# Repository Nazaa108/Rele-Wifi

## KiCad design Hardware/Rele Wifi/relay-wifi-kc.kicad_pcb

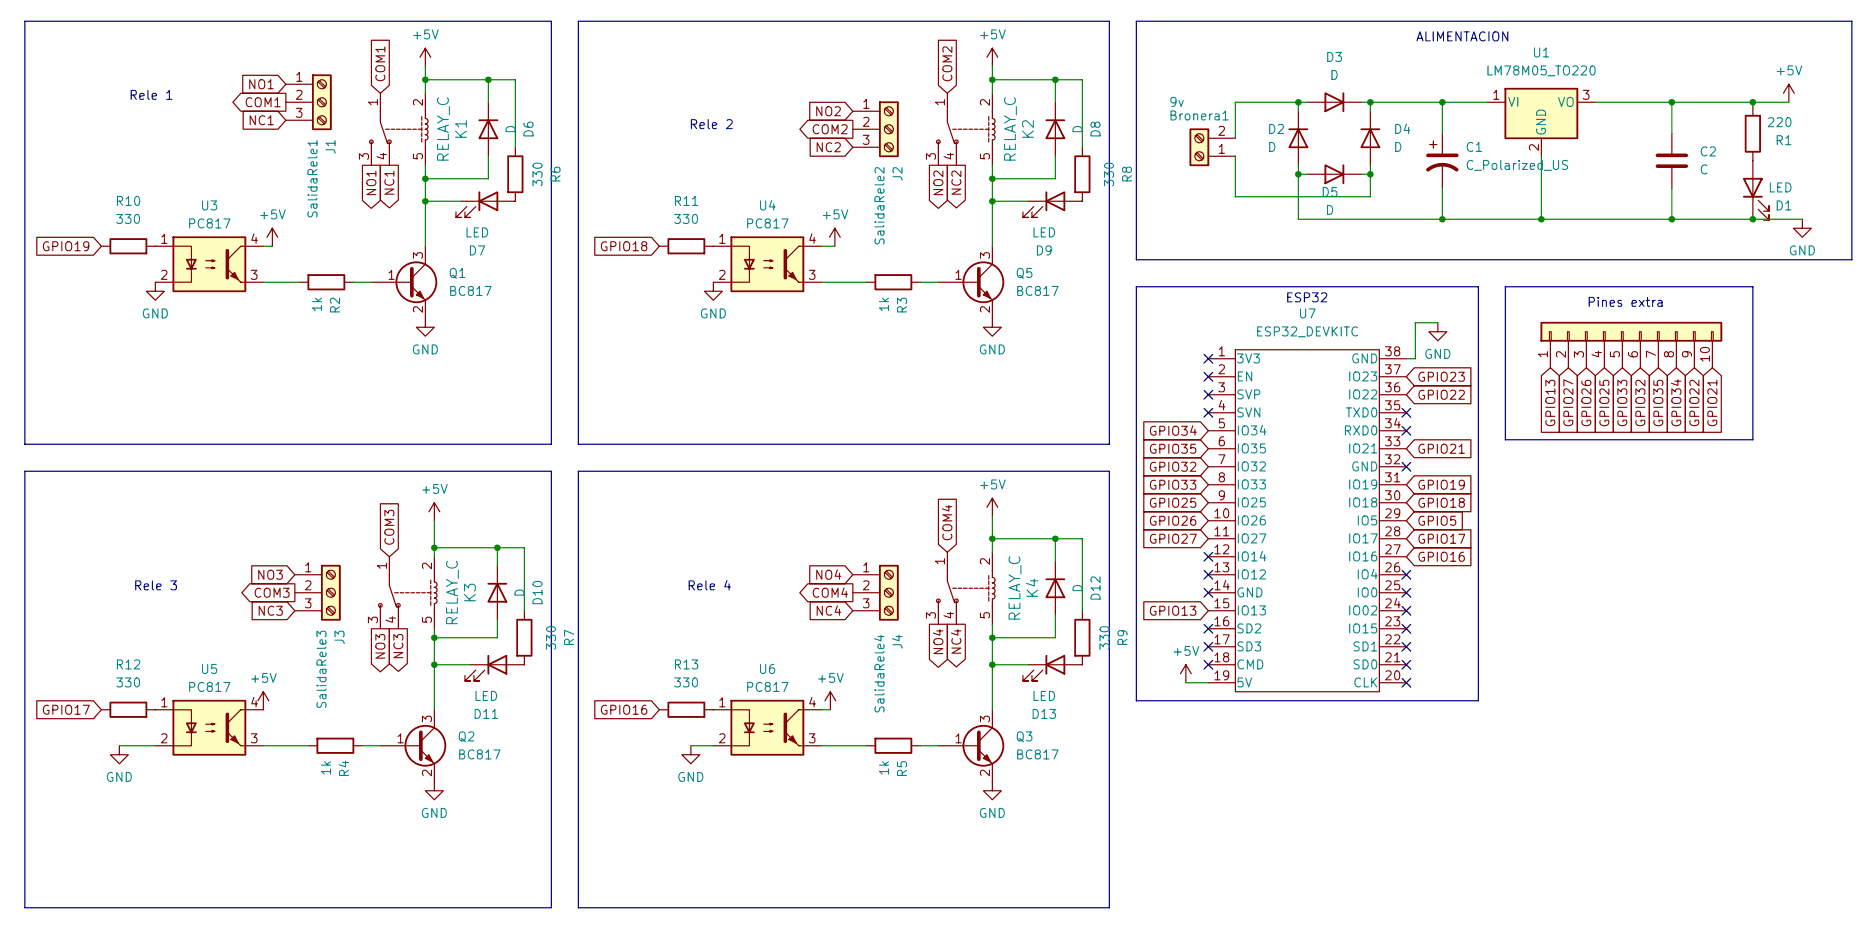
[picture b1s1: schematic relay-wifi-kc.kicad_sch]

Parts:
Bronera1: 9v; TerminalBlock_Altech_AK300-2_P5.00mm
C1: C_Polarized_US; CP_EIA-7343-15_Kemet-W
C2: C; C_0805_2012Metric_Pad1.18x1.45mm_HandSolder
D1: LED; PinSocket_1x02_P2.54mm_Vertical
D2, D3, D4, D5, D6, D8, D10, D12: D; D_SMA
D7, D9, D11, D13: LED; Altech_AK300_1x02_P5.00mm_45-Degree
J1: SalidaRele1; TerminalBlock_Altech_AK300-3_P5.00mm
J2: SalidaRele2; TerminalBlock_Altech_AK300-3_P5.00mm
J3: SalidaRele3; TerminalBlock_Altech_AK300-3_P5.00mm
J4: SalidaRele4; TerminalBlock_Altech_AK300-3_P5.00mm
J5: Conn_01x10; PinSocket_1x10_P2.54mm_Vertical
K1, K2, K3, K4: RELAY_C; Relay_SPDT_SANYOU_SRD_Series_Form_C
Q1, Q2, Q3, Q5: BC817; SOT-23
R1: 220; R_0805_2012Metric_Pad1.20x1.40mm_HandSolder
R2, R3, R4, R5: 1k; R_0805_2012Metric_Pad1.20x1.40mm_HandSolder
R6, R7, R8, R9, R10, R11, R12, R13: 330; R_0805_2012Metric_Pad1.20x1.40mm_HandSolder
U1: LM78M05_TO220; TO-252-2
U3, U4, U5, U6: PC817; DIP-4_W7.62mm_SMDSocket_SmallPads
U7: ESP32_DEVKITC; ESP32S

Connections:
+5V: C2.1, D6.1 (K), D8.1 (K), D10.1 (K), D12.1 (K), K1.2, K2.2, K3.2, K4.2, R1.2, R6.1, R7.1, R8.1, R9.1, U1.3 (VO), U3.4, U4.4, U5.4, U6.4, U7.19 (5V)
COM1: J1.2, K1.1
COM2: J2.2, K2.1
COM3: J3.2, K3.1
COM4: J4.2, K4.1
GND: C1.2, C2.2, D1.1 (K), D2.2 (A), D5.2 (A), Q1.2 (E), Q2.2 (E), Q3.2 (E), Q5.2 (E), U1.2 (GND), U3.2, U4.2, U5.2, U6.2, U7.38 (GND)
GPIO5: U7.29 (IO5)
GPIO13: J5.1, U7.15 (IO13)
GPIO16: R13.1, U7.27 (IO16)
GPIO17: R12.1, U7.28 (IO17)
GPIO18: R11.1, U7.30 (IO18)
GPIO19: R10.1, U7.31 (IO19)
GPIO21: J5.10, U7.33 (IO21)
GPIO22: J5.9, U7.36 (IO22)
GPIO23: U7.37 (IO23)
GPIO25: J5.4, U7.9 (IO25)
GPIO26: J5.3, U7.10 (IO26)
GPIO27: J5.2, U7.11 (IO27)
GPIO32: J5.6, U7.7 (IO32)
GPIO33: J5.5, U7.8 (IO33)
GPIO34: J5.8, U7.5 (IO34)
GPIO35: J5.7, U7.6 (IO35)
NC1: J1.3, K1.4
NC2: J2.3, K2.4
NC3: J3.3, K3.4
NC4: J4.3, K4.4
NO1: J1.1, K1.3
NO2: J2.1, K2.3
NO3: J3.1, K3.3
NO4: J4.1, K4.3
unnamed: Bronera1.1, D4.2 (A), D5.1 (K)
unnamed: Bronera1.2, D2.1 (K), D3.2 (A)
unnamed: D1.2 (A), R1.1
unnamed: C1.1, D3.1 (K), D4.1 (K), U1.1 (VI)
unnamed: D6.2 (A), D7.1 (K), K1.5, Q1.3 (C)
unnamed: D7.2 (A), R6.2
unnamed: D8.2 (A), D9.1 (K), K2.5, Q5.3 (C)
unnamed: D9.2 (A), R8.2
unnamed: D10.2 (A), D11.1 (K), K3.5, Q2.3 (C)
unnamed: D11.2 (A), R7.2
unnamed: D12.2 (A), D13.1 (K), K4.5, Q3.3 (C)
unnamed: D13.2 (A), R9.2
unnamed: Q1.1 (B), R2.1
unnamed: Q2.1 (B), R4.1
unnamed: Q3.1 (B), R5.1
unnamed: Q5.1 (B), R3.1
unnamed: R2.2, U3.3
unnamed: R3.2, U4.3
unnamed: R4.2, U5.3
unnamed: R5.2, U6.3
unnamed: R10.2, U3.1
unnamed: R11.2, U4.1
unnamed: R12.2, U5.1
unnamed: R13.2, U6.1

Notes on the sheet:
Rele 4
Rele 2
ESP32
Rele 3
Rele 1
Pines extra
ALIMENTACION

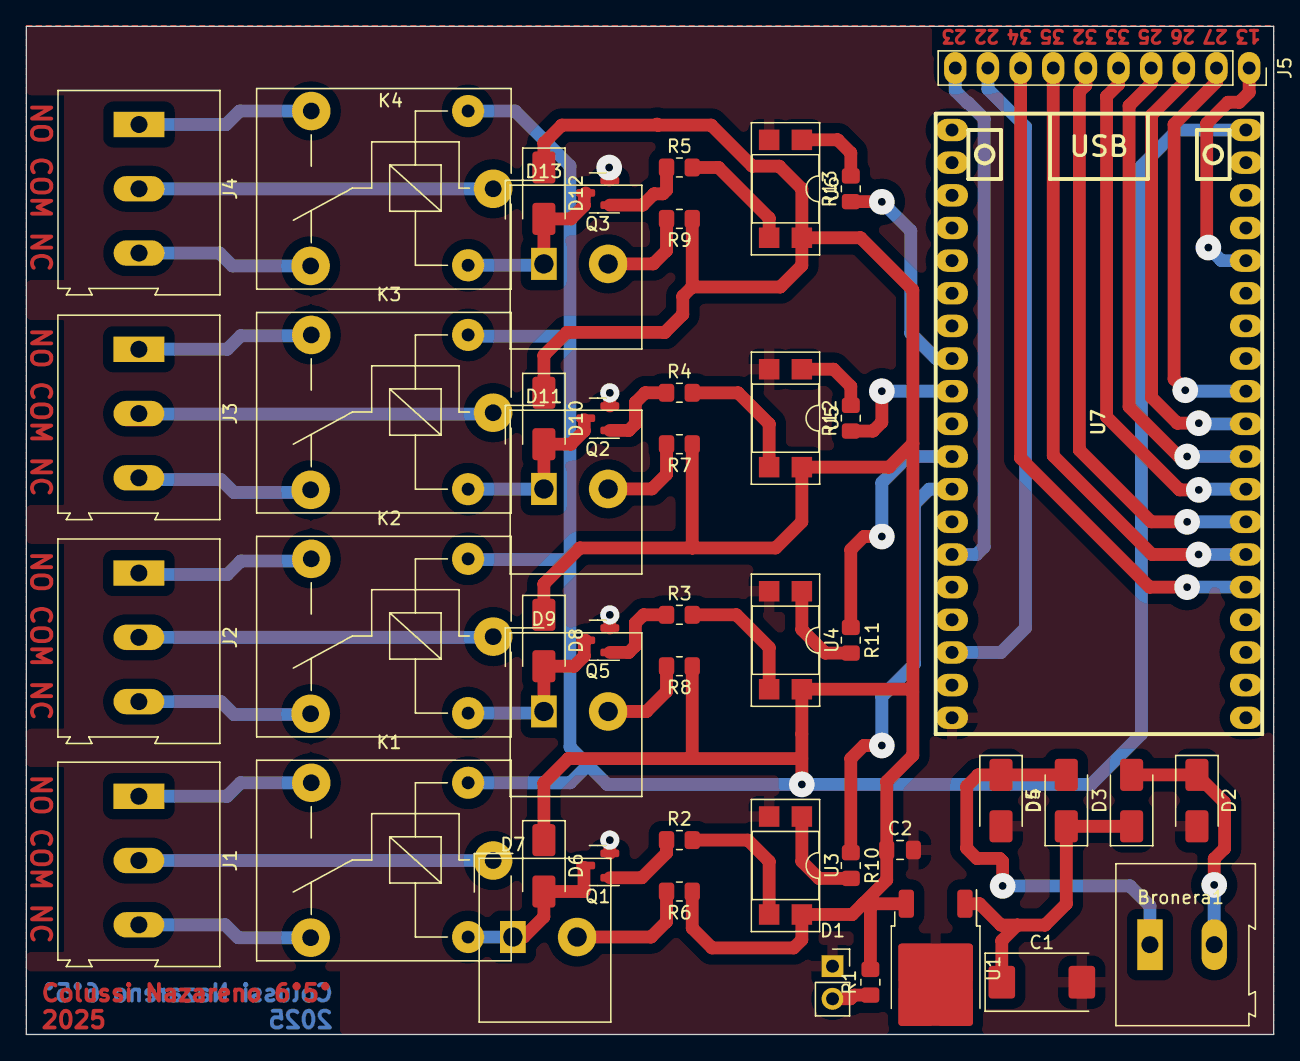
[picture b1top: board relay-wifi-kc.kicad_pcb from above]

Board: 2 copper layers, 97.0 x 78.4 mm, 48 parts (0 on the bottom side), 52 nets.

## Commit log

2025-04-30 Esquematico y PCB
2025-05-19 Esquematico y PCB V3
2025-06-03 Esquematico y PCB V4
2025-06-18 Esquematico y PCB V5
2025-06-18 Esquematico y PCB V6
2025-06-23 Esquematico y PCB V7
2025-06-25 Esquematico y PCB V8
2025-06-25 Esquematico y PCB V8.1
2025-11-05 Rele Wifi
2025-11-26 Rele wifi FINAL
